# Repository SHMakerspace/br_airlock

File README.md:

# br_airlock
A new design for the Boileroom Airlock system

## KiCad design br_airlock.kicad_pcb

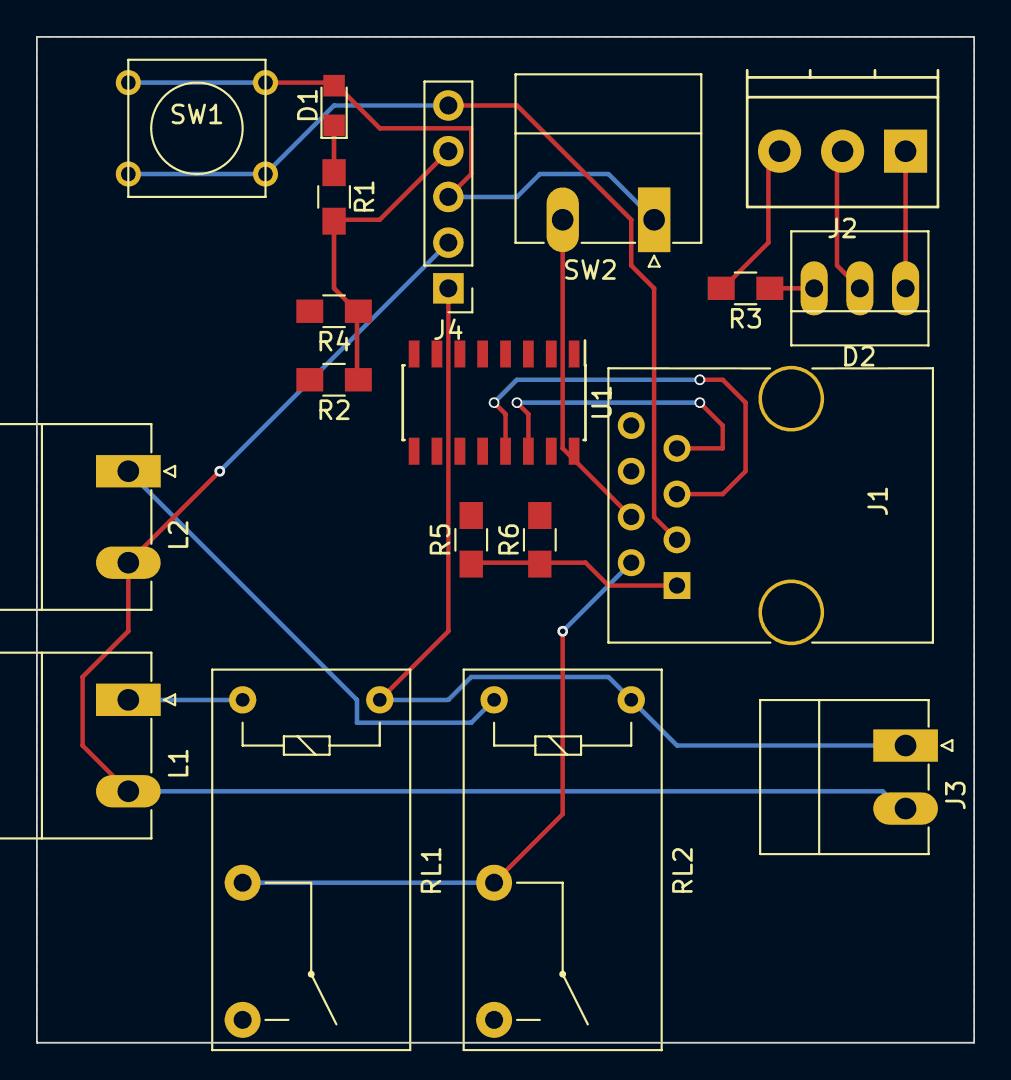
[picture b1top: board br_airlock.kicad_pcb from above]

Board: 2 copper layers, 52.1 x 55.9 mm, 19 parts (0 on the bottom side), 15 nets.

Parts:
D1: Power; LED_0805
D2: LED_Dual_AAC; PINHEAD1-3
J1: RJ45_LEDS; RJ45_8
J2: LEDS; TerminalBlock_Pheonix_PT-3.5mm_3pol
J3: 24v Power; PhoenixContact_MC-G_02x3.50mm_Angled
J4: CONN_01X05; Pin_Header_Straight_1x05_Pitch2.54mm
L1: Magnet Plate; PhoenixContact_MC-G_02x5.08mm_Angled
L2: Door Strike; PhoenixContact_MC-G_02x5.08mm_Angled
R1, R2, R3, R4, R5, R6: R; R_0805_HandSoldering
RL1, RL2: FINDER-36.11-4301; Relay_SPST-NO_OMRON-G5Q
SW1: Door Release; SW_PUSH_SMALL
SW2: SW_Reed; PhoenixContact_MC-G_02x5.08mm_Angled
U1: PCF8574; SOIC-16_3.9x9.9mm_Pitch1.27mm

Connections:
+24V: J3.1, J4.1, RL1.11, RL2.11
DO_Open_Req: J1.3, J4.5, SW1.2
GND: J1.2, J2.3, J4.4, R1.2, R2.1, R3.2, R4.1, RL1.A1, RL2.A1, U1.1, U1.2, U1.3, U1.8
GNDA: J3.2, J4.2, L1.2, L2.2
unnamed: D1.1, R1.1
unnamed: D2.1, J2.1
unnamed: D2.2, J2.2
unnamed: D2.3, R3.1
unnamed: J1.5, U1.13
unnamed: J1.6, R5.2, U1.15
unnamed: J1.7, R6.2, U1.14
unnamed: J1.4, SW2.2
unnamed: L1.1, RL1.14
unnamed: L2.1, RL2.14
VCC: D1.2, J1.1, J4.3, R5.1, R6.1, SW1.1, SW2.1, U1.16

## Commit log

2017-04-19 Initial designing - Added libraries - Fleshed out schematic
2017-04-19 More additions. Thinking I'm running out of pins on the RJ45s, might look into a simple i/o expander.
2017-04-19 Switched to a PCF8754 I/O Expander. Kinda wanted to always play with one.
2017-04-20 More work. Relay needs looking at, and a VERY rough visualisation of a PCB
